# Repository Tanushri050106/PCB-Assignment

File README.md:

View this project on [CADLAB.io](https://cadlab.io/project/29195). 

# PCB-Assignment

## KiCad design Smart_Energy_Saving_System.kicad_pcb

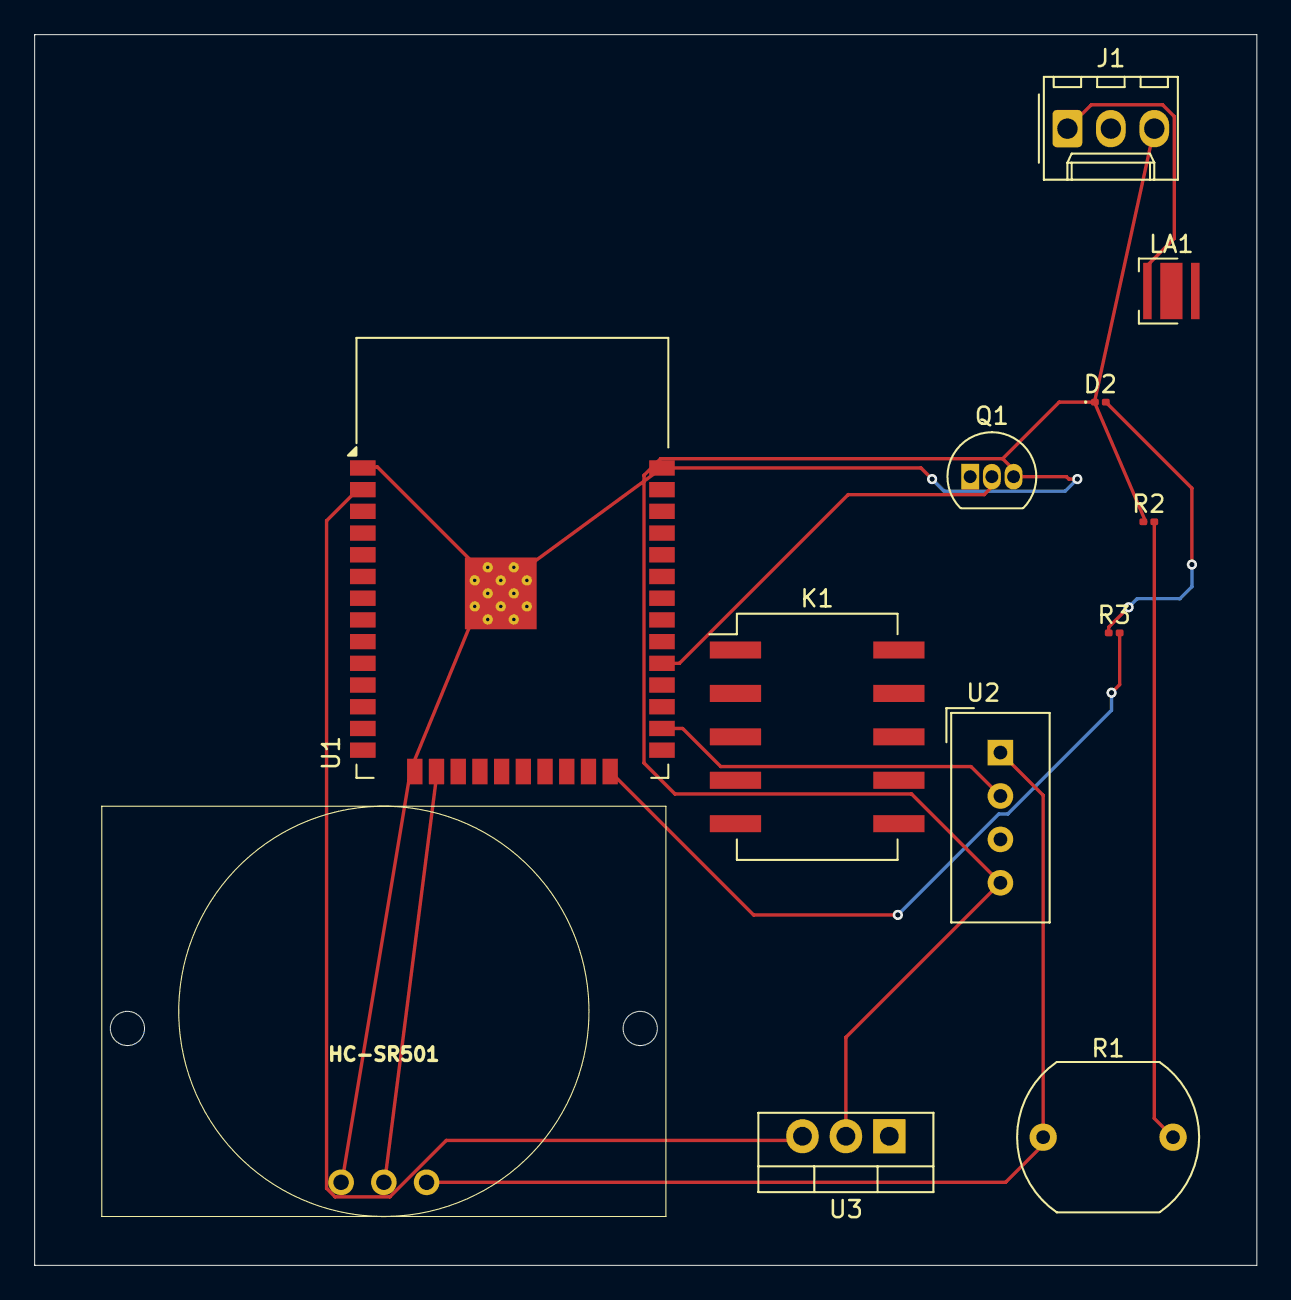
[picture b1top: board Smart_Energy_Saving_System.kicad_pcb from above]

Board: 2 copper layers, 71.5 x 72.0 mm, 12 parts (0 on the bottom side), 10 nets.

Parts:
D2: LED; LED_0201_0603Metric
HC-SR501: HC-SR501
J1: Conn_Shielded_Pair; Molex_KK-254_AE-6410-03A_1x03_P2.54mm_Vertical
K1: Relay_SPDT; Relay_DPDT_FRT5_SMD
LA1: Lamp; LED_Cree-XP
Q1: BC547; TO-92_Inline
R1: LDR03; R_LDR_10x8.5mm_P7.6mm_Vertical
R2: 10kΩ; R_0201_0603Metric
R3: 220Ω; R_0201_0603Metric
U1: ESP32-WROOM-32
U2: DHT11; Aosong_DHT11_5.5x12.0_P2.54mm
U3: LM7805_TO220; TO-220-3_Vertical

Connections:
+3.3V: HC-SR501.3 (VCC), R1.1, U2.1 (VDD)
/bjt_b: Q1.2 (B), U1.29 (IO5)
/con_in: U1.2 (VDD), U3.3 (VO)
/led: R3.2, U1.24 (IO2)
/neutral: J1.1 (In1), LA1.1 (-)
/pir: HC-SR501.2 (DATA), U1.16 (IO13)
/temp: U1.26 (IO4), U2.2 (DATA)
GND: D2.1 (K), HC-SR501.1 (GND), J1.3 (Ext), Q1.3 (E), R2.1, U1.1 (GND), U1.15 (GND), U1.38 (GND), U1.39 (GND), U2.4 (GND), U3.2 (GND)
unnamed: D2.2 (A), R3.1
unnamed: R1.2, R2.2

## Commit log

2025-04-07 pcb assignment
2025-04-07 Backlink to CADLAB.io has been added.
